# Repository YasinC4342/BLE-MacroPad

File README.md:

# Description
The MacroPad is a general use macro keypad, designed for ECAD, CAD, Photoshop, Blender and many other professionnal softwares. Its purpose is to make multiple combinations within one click, so shortcuts (ex : CTRL + ALT + SHIFT or simply write lots of words). It will be working on both BLE and USB HID.

# Why i made this ?

My goal was to make 3D models quickly for the customers who needs it earlier than expected, and also for blender if i ever forgot of which combination i use for making a Bezel for example. Since i have a compact keyboard (about 60-65%), i needed more keys without sacrificing my workspace and also to put it on the side of the desk when i doesn't need it. Anyway, here is my first prototype (i cannot 3d print parts now because I am in the process of moving but as soon as possible) :
Link : [**https://wokwi.com/projects/478323132743048193**](https://wokwi.com/projects/478323132743048193)

For information, i used examples of the libraries and merge all the examples in one code (with adjustements of course) to see if it works. Unfortunately, i don't own any esp32 but making simulations on Wowki or Tinkercad, so no bluetooth or usb, just basic testing.
 
# Features
- O.96inch OLED display
- 12 adressable RGB LEDs
- 3x4 Cherry MX switches
- USB type C
- Obviously works on bluetooth and USB HID
- A rotary encoder for controling volume with ease, for example.

# Requirements
The required components are down below :

| ID | Reference                                         | Designation                                 | Quantity | Value              | Price EUR  | Supplier   | Links                                                                                                                                                                                                                                                                    |
|----|---------------------------------------------------|---------------------------------------------|----------|--------------------|------------|------------|--------------------------------------------------------------------------------------------------------------------------------------------------------------------------------------------------------------------------------------------------------------------------|
| 1  | C1, C2, C3, C4, C5, C6, C7, C8, C9, C10, C11, C12 | 0805 SMD Capacitor                          | 12       | 0.1uF              | 1,8 €      | Aliexpress | [Link](https://www.aliexpress.com/item/1005012588693858.html?spm=a2g0o.cart.0.0.49d538daiCbZka&mp=1&pdp_npi=6%40dis%21EUR%21EUR%207.19%21EUR%203.59%21%21EUR%203.59%21%21%21%400b15834017924999145227292e0d64%2112000058767763112%21ct%21FR%214218883440%21%211%210%21)  |
| 2  | C13                                               | 0805 SMD Capacitor                          | 1        | 10uF               | 1,8 €      | Aliexpress | [Link](https://www.aliexpress.com/item/1005012588693858.html?spm=a2g0o.cart.0.0.49d538daiCbZka&mp=1&pdp_npi=6%40dis%21EUR%21EUR%207.19%21EUR%203.59%21%21EUR%203.59%21%21%21%400b15834017924999145227292e0d64%2112000058767763112%21ct%21FR%214218883440%21%211%210%21)  |
| 3  | C14                                               | Tantalum Capacitor, Kemet-A                 | 1        | 10uF               | 1,32 €     | Aliexpress | [Link](https://www.aliexpress.com/item/32698733093.html?spm=a2g0o.cart.0.0.5f4c38dagRCLxs&mp=1&pdp_npi=6%40dis%21EUR%21EUR%201.32%21EUR%201.32%21%21EUR%201.32%21%21%21%400b88abba17925010044955313e0ce6%2110000000254411173%21ct%21FR%214218883440%21%211%210%21)       |
| 4  | C15                                               | Tantalum Capacitor, Kemet-A                 | 1        | 22uF               | 1,59 €     | Aliexpress | [Link](https://www.aliexpress.com/item/32698733093.html?spm=a2g0o.cart.0.0.5f4c38dagRCLxs&mp=1&pdp_npi=6%40dis%21EUR%21EUR%201.59%21EUR%201.59%21%21EUR%201.59%21%21%21%400b88abba17925010044955313e0ce6%2110000000254411174%21ct%21FR%214218883440%21%211%210%21)       |
| 5  | D1, D2, D3, D4, D5, D6, D7, D8, D9, D10, D11, D12 | SK6812 Mini Reversed SMD RGB LEDs           | 12       | SK6812             | 4,39 €     | Aliexpress | [Link](https://www.aliexpress.com/item/1005005186515165.html?spm=a2g0o.cart.0.0.49d538daiCbZka&mp=1&pdp_npi=6%40dis%21EUR%21EUR%204.39%21EUR%204.39%21%21EUR%204.39%21%21%21%400b15834017924999145227292e0d64%2112000032026120161%21ct%21FR%214218883440%21%211%210%21)  |
| 6  | D13                                               | 1206 SMD Diode                              | 1        | Diode              | -          | Aliexpress | **Already own the component**                                                                                                                                                                                                                                            |
| 7  | J1                                                | USB-C Female connector 12 pin               | 1        | USB_C_female_14P   | 2,18 €     | Aliexpress | [Link](https://www.aliexpress.com/item/1005005371954812.html?spm=a2g0o.cart.0.0.10c238daxwhGx7&mp=1&pdp_npi=6%40dis%21EUR%21EUR%202.18%21EUR%202.18%21%21EUR%202.18%21%21%21%400b88abba17925006340776757e0ce6%2112000032786473720%21ct%21FR%214218883440%21%211%210%21)  |
| 8  | R1                                                | 1206 SMD Resistor                           | 1        | 470R               | 0,95 €     | Aliexpress | [Link](https://www.aliexpress.com/item/1005012304341288.html?spm=a2g0o.cart.0.0.49d538daiCbZka&mp=1&pdp_npi=6%40dis%21EUR%21EUR%207.56%21EUR%203.79%21%21EUR%203.79%21%21%21%400b15834017924999145227292e0d64%2112000058017651589%21ct%21FR%214218883440%21%211%210%21)  |
| 9  | R2, R3, R5, R6                                    | 1206 SMD Resistor                           | 4        | 5.1K               | 0,95 €     | Aliexpress | [Link](https://www.aliexpress.com/item/1005012304341288.html?spm=a2g0o.cart.0.0.49d538daiCbZka&mp=1&pdp_npi=6%40dis%21EUR%21EUR%207.56%21EUR%203.79%21%21EUR%203.79%21%21%21%400b15834017924999145227292e0d64%2112000058017651589%21ct%21FR%214218883440%21%211%210%21)  |
| 10 | R4                                                | 1206 SMD Resistor                           | 1        | 10K                | 0,95 €     | Aliexpress | [Link](https://www.aliexpress.com/item/1005012304341288.html?spm=a2g0o.cart.0.0.49d538daiCbZka&mp=1&pdp_npi=6%40dis%21EUR%21EUR%207.56%21EUR%203.79%21%21EUR%203.79%21%21%21%400b15834017924999145227292e0d64%2112000058017651589%21ct%21FR%214218883440%21%211%210%21)  |
| 11 | R7                                                | 1206 SMD Resistor                           | 1        | 1.8K               | 0,95 €     | Aliexpress | [Link](https://www.aliexpress.com/item/1005012304341288.html?spm=a2g0o.cart.0.0.49d538daiCbZka&mp=1&pdp_npi=6%40dis%21EUR%21EUR%207.56%21EUR%203.79%21%21EUR%203.79%21%21%21%400b15834017924999145227292e0d64%2112000058017651589%21ct%21FR%214218883440%21%211%210%21)  |
| 12 | R9                                                | 2010 SMD Resistor                           | 1        | 0R                 | -          | Aliexpress | **Already own the component**                                                                                                                                                                                                                                            |
| 13 | S1, S2, S3, S4, S5, S6, S7, S8, S9, S10, S11, S12 | Cherry MX1A-11NA Switches                   | 12       | MX1A-11NA          | 5,30 €     | Aliexpress | [Link](https://www.aliexpress.com/item/1005008089864080.html?spm=a2g0o.cart.0.0.49d538daiCbZka&mp=1&pdp_npi=6%40dis%21EUR%21EUR%202.65%21EUR%202.65%21%21EUR%202.65%21%21%21%400b15834017924999145227292e0d64%2112000045838677521%21ct%21FR%214218883440%21%212%210%21)  |
| 14 | S13                                               | PEC11R Rotary encoder                       | 1        | PEC12R_Encoder     | 3,99 €     | Aliexpress | [Link](https://www.aliexpress.com/item/1005007391341287.html?spm=a2g0o.cart.0.0.10c238daxwhGx7&mp=1&pdp_npi=6%40dis%21EUR%21EUR%2011.61%21EUR%203.99%21%21EUR%203.99%21%21%21%400b88abba17925006340776757e0ce6%2112000040556905956%21ct%21FR%214218883440%21%211%210%21) |
| 15 | SW1                                               | SPDT Slide switch                           | 1        | SW_SPDT            | -          | Aliexpress | **Already own the component**                                                                                                                                                                                                                                            |
| 16 | SW2                                               | Push button 6x3.5mm                         | 1        | SW_Push            | 3,59 €     | Aliexpress | [Link](https://www.aliexpress.com/item/1005007177692594.html?spm=a2g0o.cart.0.0.10c238daxwhGx7&mp=1&pdp_npi=6%40dis%21EUR%21EUR%203.59%21EUR%203.59%21%21EUR%203.59%21%21%21%400b88abba17925006340776757e0ce6%2112000039712603252%21ct%21FR%214218883440%21%211%210%21)  |
| 17 | U1                                                | ESP32-S3-WROOM-1                            | 1        | ESP32-S3-WROOM-1   | 6,59 €     | Aliexpress | [Link](https://www.aliexpress.com/item/1005009314619102.html?spm=a2g0o.cart.0.0.49d538daiCbZka&mp=1&pdp_npi=6%40dis%21EUR%21EUR%203.77%21EUR%203.39%21%21EUR%203.39%21%21%21%400b15834017924999145227292e0d64%2112000048716802392%21ct%21FR%214218883440%21%211%210%21)  |
| 18 | U2                                                | 0.96" OLED Display module                   | 1        | 0,96"  OLED Module | 2,56 €     | Aliexpress | [Link](https://www.aliexpress.com/item/1005006141235306.html?spm=a2g0o.cart.0.0.10c238daxwhGx7&mp=1&pdp_npi=6%40dis%21EUR%21EUR%202.56%21EUR%202.56%21%21EUR%202.56%21%21%21%400b88abba17925006340776757e0ce6%2112000035944225407%21ct%21FR%214218883440%21%211%210%21)  |
| 20 | PCB                                               | Main PCB                                    | 1        | PCB                | 3,57 €     | Aliexpress | [Link](https://cart.jlcpcb.com/fr/quote?spm=jlcpcb.Public.2006)                                                                                                                                                                                                           
| **Total** | **43,88 €** | **49,24 $** |

**AI Disclosure:**
During this project, I used AI to help with debugging KiCad DRC errors and to assist in writing firmware, and to check if my circuit is fine WITHOUT listing any components, just giving me advice and i did on my own and figured out later.

For 3d parts, I wiil 3d print them, so not included in the list of shipping or buying.

# Downloads
Download the complete hardware design package from the [**v2.0.0 Release**](https://github.com/YasinC4342/BLE-MacroPad/releases/tag/v2.0.0).

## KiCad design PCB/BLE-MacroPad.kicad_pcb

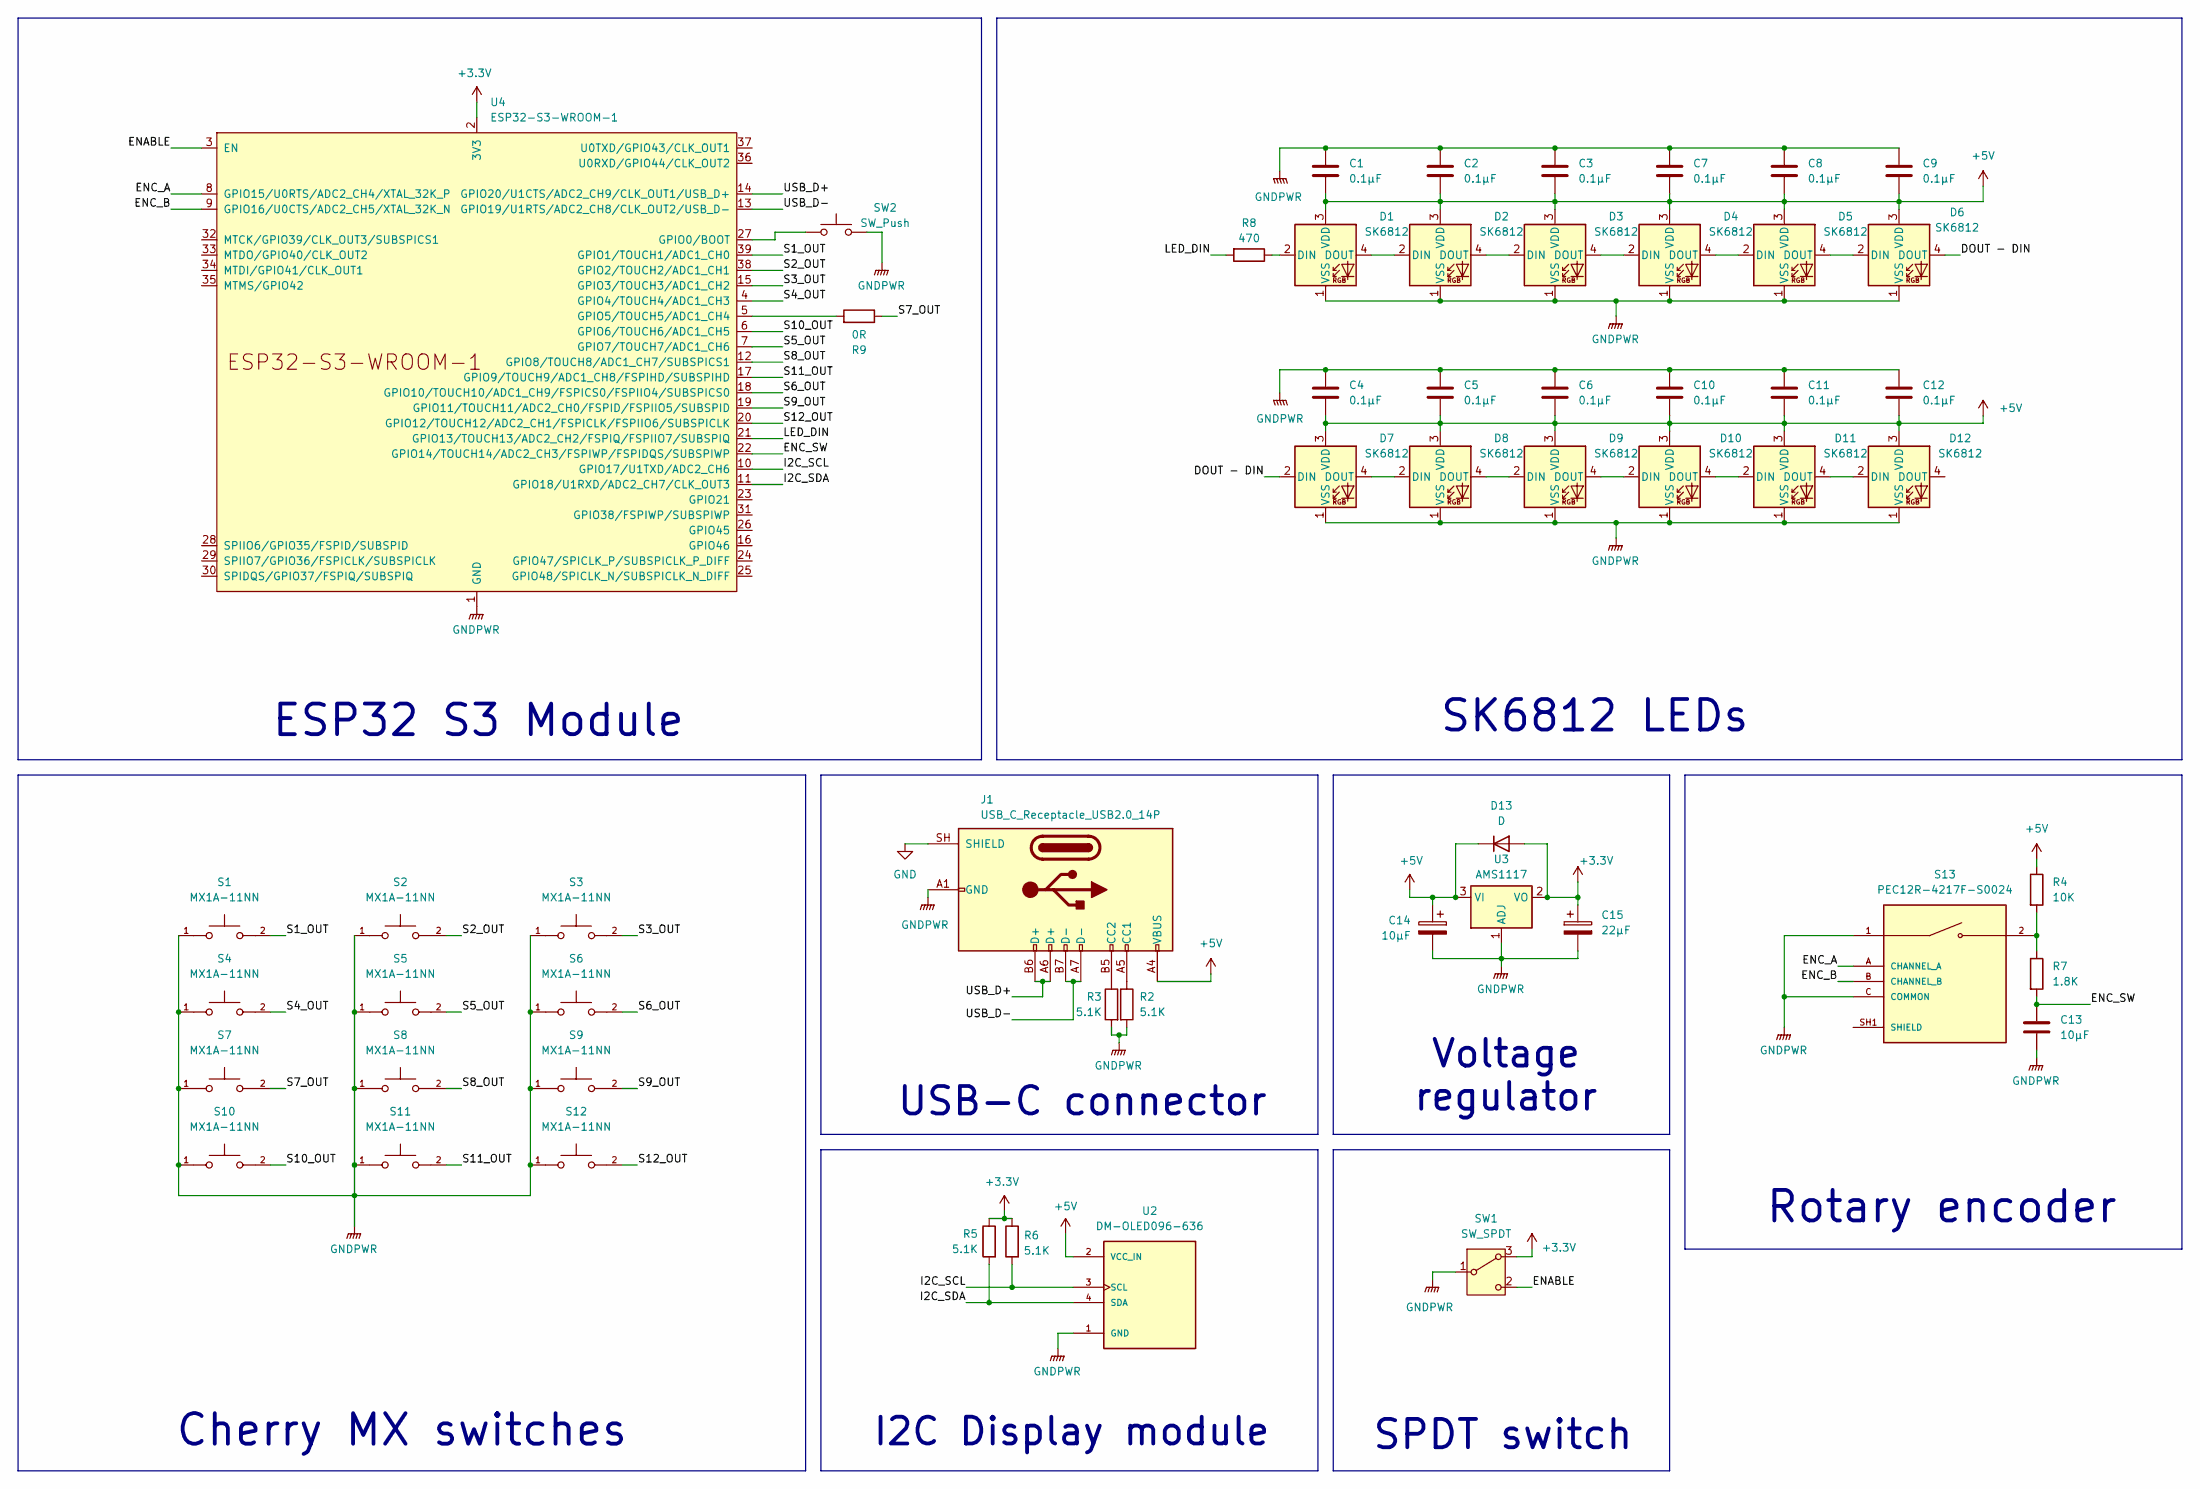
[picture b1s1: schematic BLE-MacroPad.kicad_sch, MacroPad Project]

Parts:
C1, C2, C3, C4, C5, C6, C7, C8, C9, C10, C11, C12: 0.1µF; C_0805_2012Metric_Pad1.18x1.45mm_HandSolder
C13: 10µF; C_0805_2012Metric_Pad1.18x1.45mm_HandSolder
C14: 10µF; CP_EIA-3216-18_Kemet-A_HandSolder
C15: 22µF; CP_EIA-3216-18_Kemet-A_HandSolder
D1, D2, D3, D4, D5, D6, D7, D8, D9, D10, D11, D12: SK6812; MX_SK6812MINI-E
D13: D; D_1206_3216Metric
J1: USB_C_Receptacle_USB2.0_14P; USB_C_Receptacle_Palconn_UTC16-G
R2, R3, R5, R6: 5.1K; R_1206_3216Metric_Pad1.30x1.75mm_HandSolder
R4: 10K; R_1206_3216Metric_Pad1.30x1.75mm_HandSolder
R7: 1.8K; R_1206_3216Metric_Pad1.30x1.75mm_HandSolder
R8: 470; R_1206_3216Metric_Pad1.30x1.75mm_HandSolder
R9: 0R; R_2010_5025Metric_Pad1.40x2.65mm_HandSolder
S1, S2, S3, S4, S5, S6, S7, S8, S9, S10, S11, S12: MX1A-11NN; SW_Cherry_MX_1.00u_PCB
S13: PEC12R-4217F-S0024; XDCR_PEC12R-4217F-S0024
SW1: SW_SPDT; SW_Slide_SPDT_Angled_CK_OS102011MA1Q
SW2: SW_Push; SW_PUSH_1P1T_6x3.5mm_H5.0_APEM_MJTP1250
U2: DM-OLED096-636; MODULE_DM-OLED096-636
U3: AMS1117; SOT-223-3_TabPin2
U4: ESP32-S3-WROOM-1

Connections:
+3.3V: C15.1, D13.2 (A), R5.1, R6.1, SW1.3 (A), U3.2 (VO), U4.2 (3V3)
+5V: C1.2, C2.2, C3.2, C4.2, C5.2, C6.2, C7.2, C8.2, C9.2, C10.2, C11.2, C12.2, C14.1, D1.3 (VDD), D2.3 (VDD), D3.3 (VDD), D4.3 (VDD), D5.3 (VDD), D6.3 (VDD), D7.3 (VDD), D8.3 (VDD), D9.3 (VDD), D10.3 (VDD), D11.3 (VDD), D12.3 (VDD), D13.1 (K), J1.A4 (VBUS), J1.A9 (VBUS), J1.B4 (VBUS), J1.B9 (VBUS), R4.1, U2.2 (VCC_IN), U3.3 (VI); also elsewhere on the board
/DOUT - DIN: D6.4 (DOUT), D7.2 (DIN)
/ENABLE: SW1.2 (C), U4.3 (EN)
/ENC_A: S13.A (CHANNEL_A), U4.8 (GPIO15/U0RTS/ADC2_CH4/XTAL_32K_P)
/ENC_B: S13.B (CHANNEL_B), U4.9 (GPIO16/U0CTS/ADC2_CH5/XTAL_32K_N)
/ENC_SW: C13.1, R7.2, U4.22 (GPIO14/TOUCH14/ADC2_CH3/FSPIWP/FSPIDQS/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)
/I2C_SCL: R6.2, U2.3 (SCL), U4.10 (GPIO17/U1TXD/ADC2_CH6)
/I2C_SDA: R5.2, U2.4 (SDA), U4.11 (GPIO18/U1RXD/ADC2_CH7/CLK_OUT3)
/LED_DIN: R8.2, U4.21 (GPIO13/TOUCH13/ADC2_CH2/FSPIQ/FSPIIO7/S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)
/S1_OUT: S1.2, U4.39 (GPIO1/TOUCH1/ADC1_CH0)
/S2_OUT: S2.2, U4.38 (GPIO2/TOUCH2/ADC1_CH1)
/S3_OUT: S3.2, U4.15 (GPIO3/TOUCH3/ADC1_CH2)
/S4_OUT: S4.2, U4.4 (GPIO4/TOUCH4/ADC1_CH3)
/S5_OUT: S5.2, U4.7 (GPIO7/TOUCH7/ADC1_CH6)
/S6_OUT: S6.2, U4.18 (GPIO10/TOUCH10/ADC1_CH9/FSPICS0/FSPIIO4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)
/S7_OUT: R9.1, S7.2
/S8_OUT: S8.2, U4.12 (GPIO8/TOUCH8/ADC1_CH7/SUBSPICS1)
/S9_OUT: S9.2, U4.19 (GPIO11/TOUCH11/ADC2_CH0/FSPID/FSPIIO5/S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)
/S10_OUT: S10.2, U4.6 (GPIO6/TOUCH6/ADC1_CH5)
/S11_OUT: S11.2, U4.17 (GPIO9/TOUCH9/ADC1_CH8/FSPIHD/SUBSPIHD)
/S12_OUT: S12.2, U4.20 (GPIO12/TOUCH12/ADC2_CH1/FSPICLK/FSPIIO6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)
/USB_D+: J1.A6 (D+), J1.B6 (D+), U4.14 (GPIO20/U1CTS/ADC2_CH9/CLK_OUT1/USB_D+)
/USB_D-: J1.A7 (D-), J1.B7 (D-), U4.13 (GPIO19/U1RTS/ADC2_CH8/CLK_OUT2/USB_D-)
GND: J1.SH (SHIELD)
GNDPWR: C1.1, C2.1, C3.1, C4.1, C5.1, C6.1, C7.1, C8.1, C9.1, C10.1, C11.1, C12.1, C13.2, C14.2, C15.2, D1.1 (VSS), D2.1 (VSS), D3.1 (VSS), D4.1 (VSS), D5.1 (VSS), D6.1 (VSS), D7.1 (VSS), D8.1 (VSS), D9.1 (VSS), D10.1 (VSS), D11.1 (VSS), D12.1 (VSS), J1.A1 (GND), J1.A12 (GND), J1.B1 (GND), J1.B12 (GND), R2.2, R3.2, S1.1, S2.1, S3.1, S4.1, S5.1, S6.1, S7.1, S8.1, S9.1, S10.1, S11.1, S12.1, S13.1, S13.C (COMMON), SW1.1 (B), SW2.2, U2.1 (GND), U3.1 (ADJ), U4.1 (GND), U4.40 (GND), U4.41 (GND); also elsewhere on the board
unnamed: D1.2 (DIN), R8.1
unnamed: D1.4 (DOUT), D2.2 (DIN)
unnamed: D2.4 (DOUT), D3.2 (DIN)
unnamed: D3.4 (DOUT), D4.2 (DIN)
unnamed: D4.4 (DOUT), D5.2 (DIN)
unnamed: D5.4 (DOUT), D6.2 (DIN)
unnamed: D7.4 (DOUT), D8.2 (DIN)
unnamed 33: D8.4 (DOUT), D9.2 (DIN); also elsewhere on the board
unnamed 34: D9.4 (DOUT), D10.2 (DIN); also elsewhere on the board
unnamed: D10.4 (DOUT), D11.2 (DIN)
unnamed: D11.4 (DOUT), D12.2 (DIN)
unnamed: J1.A5 (CC1), R2.1
unnamed: J1.B5 (CC2), R3.1
unnamed: R4.2, R7.1, S13.2
unnamed: S13.SH1 (SHIELD), S13.SH2 (SHIELD)
unnamed: SW2.1, U4.27 (GPIO0/BOOT)
unnamed: R9.2, U4.5 (GPIO5/TOUCH5/ADC1_CH4)

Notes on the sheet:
ESP32 S3 Module
SK6812 LEDs
Rotary encoder
Cherry MX switches
SPDT switch
USB-C connector
Voltage regulator
I2C Display module

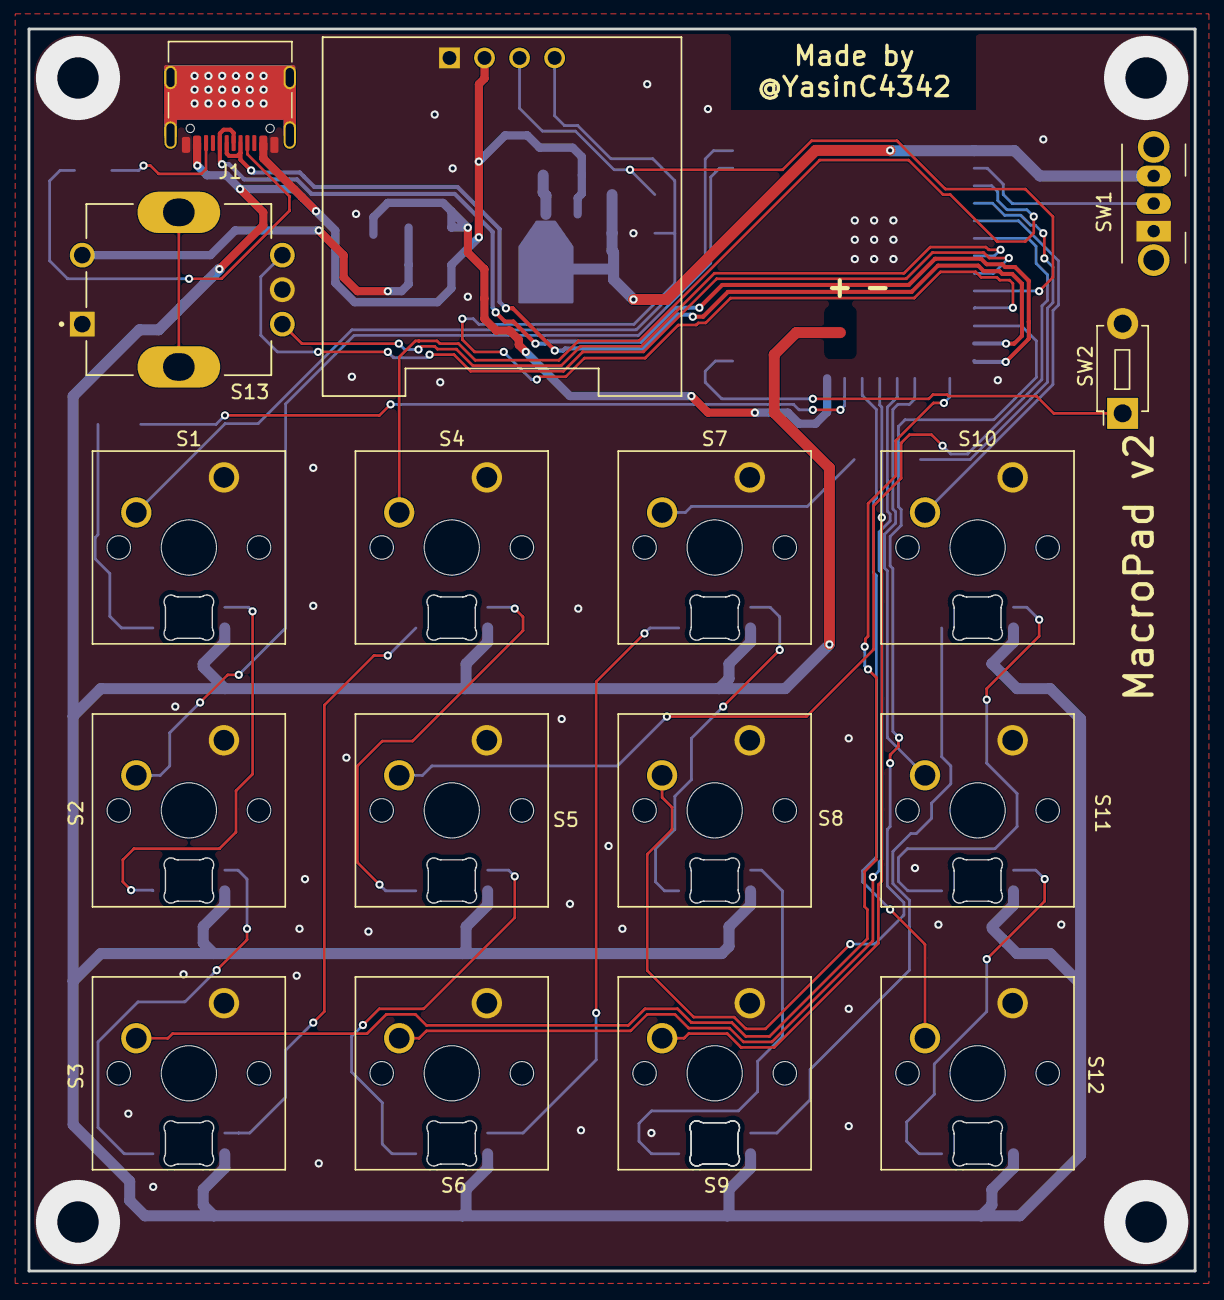
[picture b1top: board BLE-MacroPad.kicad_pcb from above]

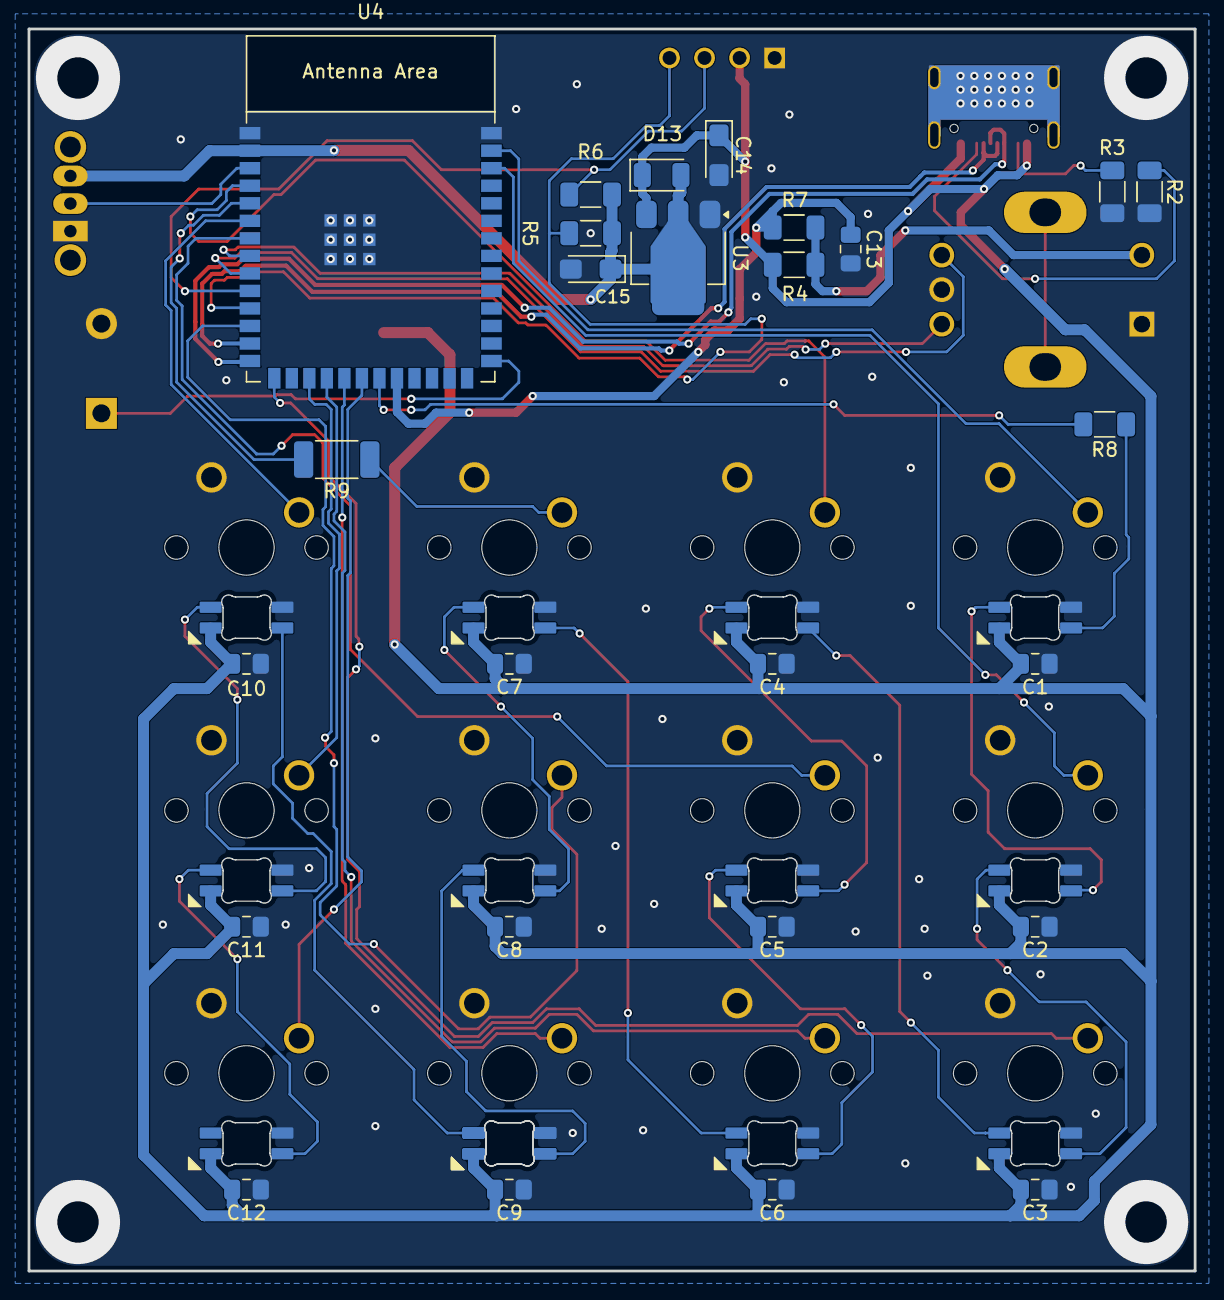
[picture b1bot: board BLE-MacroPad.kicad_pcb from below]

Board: 2 copper layers, 84.5 x 90.0 mm, 56 parts (26 on the bottom side), 42 nets.

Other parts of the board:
D9#2: SK6812; MX_SK6812MINI-E

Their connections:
+5V: D9#2.3 (VDD); also elsewhere on the board
GNDPWR: D9#2.1 (VSS); also elsewhere on the board
unnamed 33: D9#2.2 (DIN); also elsewhere on the board
unnamed 34: D9#2.4 (DOUT); also elsewhere on the board

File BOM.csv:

"Id";"Référence";"Empreinte";"Quantité";"Désignation";"Fournisseur et réf";
1;"C1, C2, C3, C4, C5, C6, C7, C8, C9, C10, C11, C12";"C_0805_2012Metric_Pad1.18x1.45mm_HandSolder";12;"0.1µF";;;
2;"C13";"C_0805_2012Metric_Pad1.18x1.45mm_HandSolder";1;"10µF";;;
3;"C14";"CP_EIA-3216-18_Kemet-A_HandSolder";1;"10µF";;;
4;"C15";"CP_EIA-3216-18_Kemet-A_HandSolder";1;"22µF";;;
5;"D1, D2, D3, D4, D5, D6, D7, D8, D9, D9, D10, D11, D12";"MX_SK6812MINI-E";13;"SK6812";;;
6;"D13";"D_1206_3216Metric";1;"D";;;
7;"J1";"USB_C_Receptacle_Palconn_UTC16-G";1;"USB_C_Receptacle_USB2.0_14P";;;
8;"R2, R3, R5, R6";"R_1206_3216Metric_Pad1.30x1.75mm_HandSolder";4;"5.1K";;;
9;"R4";"R_1206_3216Metric_Pad1.30x1.75mm_HandSolder";1;"10K";;;
10;"R7";"R_1206_3216Metric_Pad1.30x1.75mm_HandSolder";1;"1.8K";;;
11;"R8";"R_1206_3216Metric_Pad1.30x1.75mm_HandSolder";1;"470";;;
12;"R9";"R_2010_5025Metric_Pad1.40x2.65mm_HandSolder";1;"0R";;;
13;"S1, S2, S3, S4, S5, S6, S7, S8, S9, S10, S11, S12";"SW_Cherry_MX_1.00u_PCB";12;"MX1A-11NN";;;
14;"S13";"XDCR_PEC12R-4217F-S0024";1;"PEC12R-4217F-S0024";;;
15;"SW1";"SW_Slide_SPDT_Angled_CK_OS102011MA1Q";1;"SW_SPDT";;;
16;"SW2";"SW_PUSH_1P1T_6x3.5mm_H5.0_APEM_MJTP1250";1;"SW_Push";;;
17;"U2";"MODULE_DM-OLED096-636";1;"DM-OLED096-636";;;
18;"U3";"SOT-223-3_TabPin2";1;"AMS1117";;;
19;"U4";"ESP32-S3-WROOM-1";1;"ESP32-S3-WROOM-1";;;
